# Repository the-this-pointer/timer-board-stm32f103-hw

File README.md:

# Universal Timer Board Hardware
This project is the alpha version for <a href="https://github.com/the-this-pointer/timer-board-stm32f103" target="_blank">this project</a>. It's deprecated and has some blunders in PCB designs that are not fixed in these files.

The newer version of timer hardware is located <a href="https://github.com/the-this-pointer/timer-board-stm32f103-hw-2" target="_blank">here</a>

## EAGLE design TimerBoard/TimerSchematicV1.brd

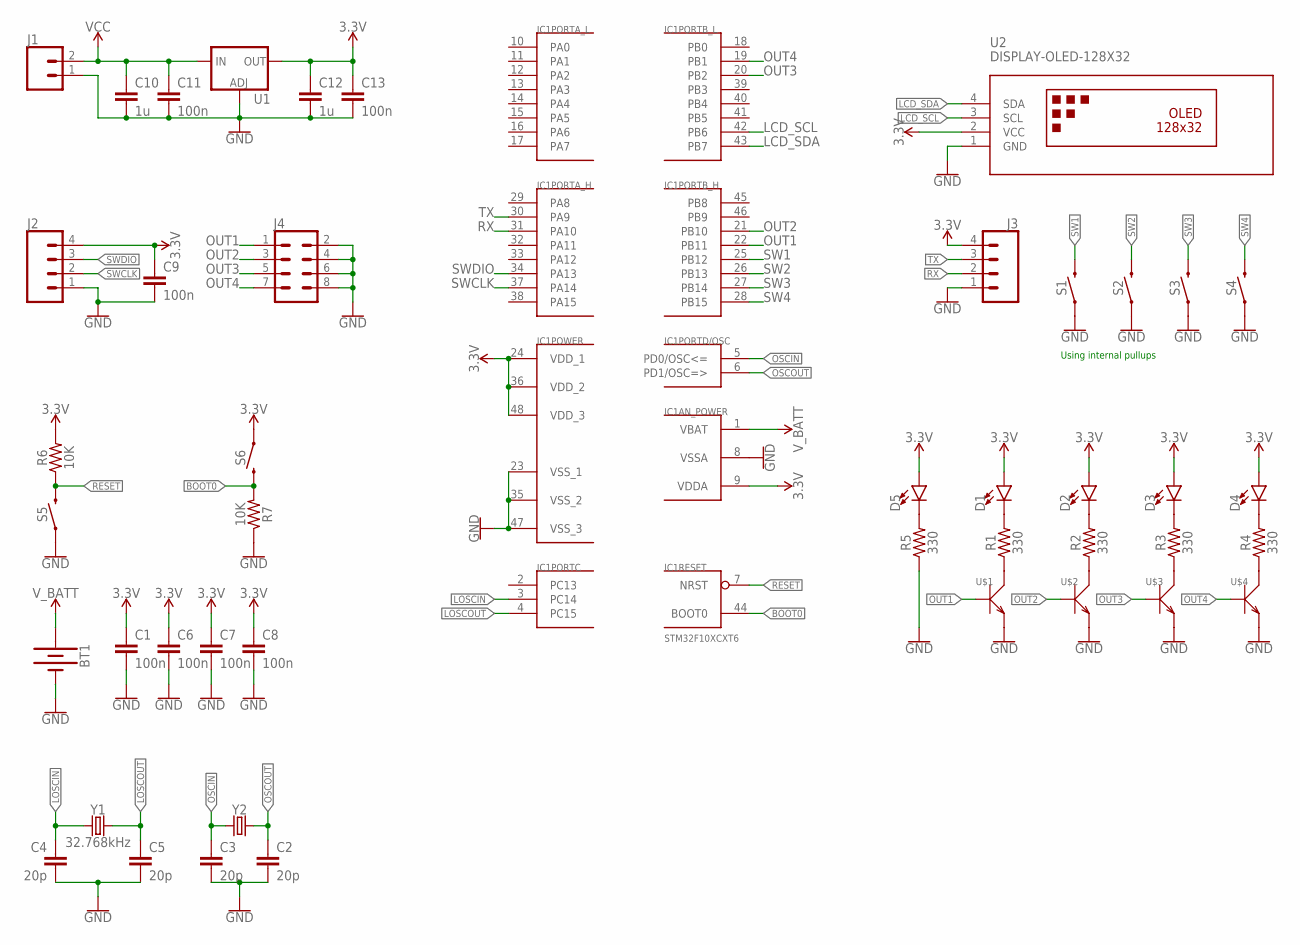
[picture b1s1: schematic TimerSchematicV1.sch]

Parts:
BT1: BATTERY-20MM_PTH; BATTCOM_20MM_PTH
C1, C6, C7, C8, C9, C11, C13: 100n; 1206
C2, C3, C4, C5: 20p; 1206
C10, C12: 1u; 1206
D1, D2, D3, D4, D5: LED1206; LED-1206
IC1: STM32F10XCXT6; TQFP48
J1: CONN_02; 1X02
J2, J3: CONN_04PTH; 1X04
J4: CONN_04X2; 2X4
R1, R2, R3, R4, R5: 330; 1206
R6, R7: 10K; 1206
S1, S2, S3, S4: MOMENTARY-SWITCH-SPST-PTH-6.0MM-KIT; TACTILE_SWITCH_PTH_6.0MM_KIT
S5, S6: MOMENTARY-SWITCH-SPST-SMD-6.0X3.5MM; TACTILE_SWITCH_SMD_6.0X3.5MM
U1: V_REG_LM1117SOT223; SOT223
U2: DISPLAY-OLED-128X32
U$1, U$2, U$3, U$4: MMBT3904LT1G; SOT-23
Y1: 32.768kHz; CRYSTAL-PTH-2X6-CYL-KIT
Y2: CRYSTALSMD-HC49UP; HC49UP

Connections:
3.3V: C1.1, C6.1, C7.1, C8.1, C9.1, C12.1, C13.1, D1.A, D2.A, D3.A, D4.A, D5.A, IC1.9 (VDDA), IC1.24 (VDD_1), IC1.36 (VDD_2), IC1.48 (VDD_3), J2.4, J3.4, R6.2, S6.1, U1.2 (OUT), U1.4 (OUT), U2.2 (VCC)
BOOT0: IC1.44 (BOOT0), R7.2, S6.2
GND: BT1.2 (-), C1.2, C2.2, C3.2, C4.2, C5.2, C6.2, C7.2, C8.2, C9.2, C10.2, C11.2, C12.2, C13.2, IC1.8 (VSSA), IC1.23 (VSS_1), IC1.35 (VSS_2), IC1.47 (VSS_3), J1.1, J2.1, J3.1, J4.2, J4.4, J4.6, J4.8, R5.1, R7.1, S1.1, S2.1, S3.1, S4.1, S5.1, U1.1 (ADJ), U2.1 (GND), U$1.2 (E), U$2.2 (E), U$3.2 (E), U$4.2 (E)
LCD_SCL: IC1.42 (PB6), U2.3 (SCL)
LCD_SDA: IC1.43 (PB7), U2.4 (SDA)
LOSCIN: C4.1, IC1.3 (PC14), Y1.1
LOSCOUT: C5.1, IC1.4 (PC15), Y1.2
unnamed: D1.C, R1.2
unnamed: D2.C, R2.2
unnamed: D3.C, R3.2
unnamed: D4.C, R4.2
unnamed: D5.C, R5.2
unnamed: R1.1, U$1.3 (C)
unnamed: R2.1, U$2.3 (C)
unnamed: R3.1, U$3.3 (C)
unnamed: R4.1, U$4.3 (C)
OSCIN: C3.1, IC1.5 (PD0/OSC<=), Y2.1
OSCOUT: C2.1, IC1.6 (PD1/OSC=>), Y2.2
OUT1: IC1.22 (PB11), J4.1, U$1.1 (B)
OUT2: IC1.21 (PB10), J4.3, U$2.1 (B)
OUT3: IC1.20 (PB2), J4.5, U$3.1 (B)
OUT4: IC1.19 (PB1), J4.7, U$4.1 (B)
RESET: IC1.7 (NRST), R6.1, S5.2
RX: IC1.31 (PA10), J3.2
SW1: IC1.25 (PB12), S1.3 (2)
SW2: IC1.26 (PB13), S2.3 (2)
SW3: IC1.27 (PB14), S3.3 (2)
SW4: IC1.28 (PB15), S4.3 (2)
SWCLK: IC1.37 (PA14), J2.2
SWDIO: IC1.34 (PA13), J2.3
TX: IC1.30 (PA9), J3.3
VCC: C10.1, C11.1, J1.2, U1.3 (IN)
V_BATT: BT1.1 (+), IC1.1 (VBAT)

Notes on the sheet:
Using internal pullups

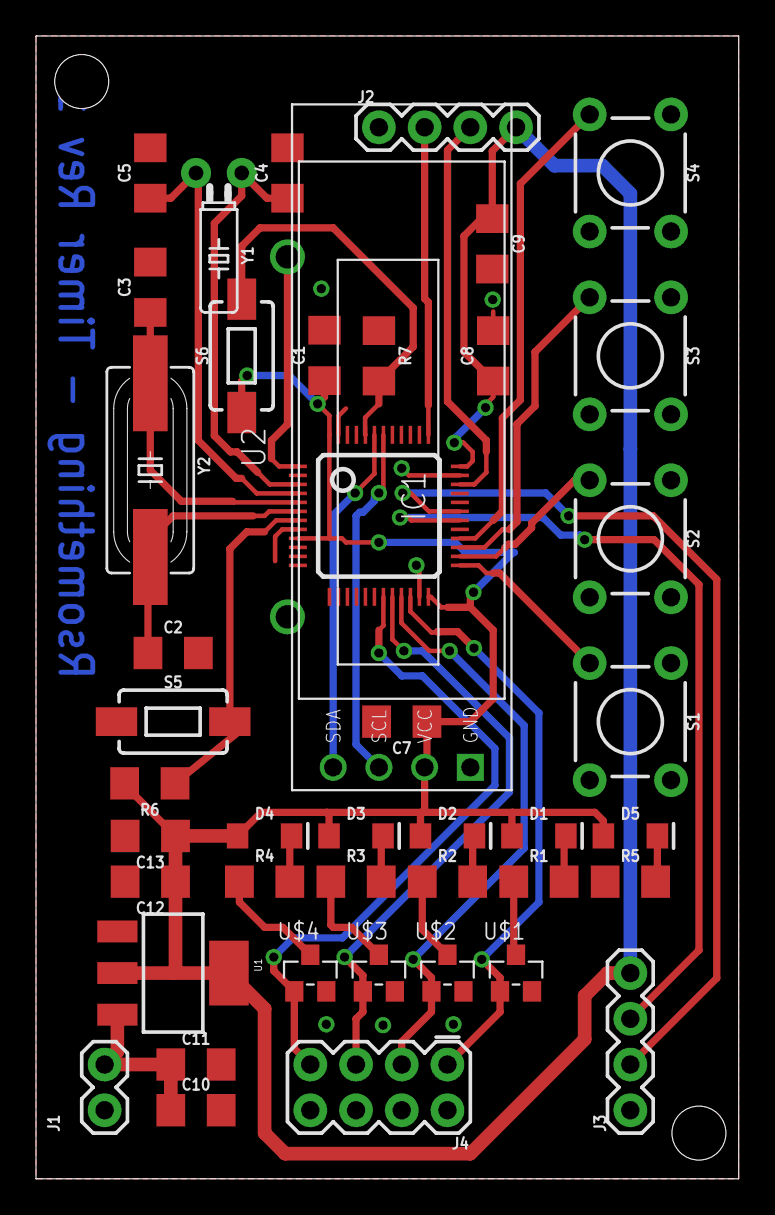
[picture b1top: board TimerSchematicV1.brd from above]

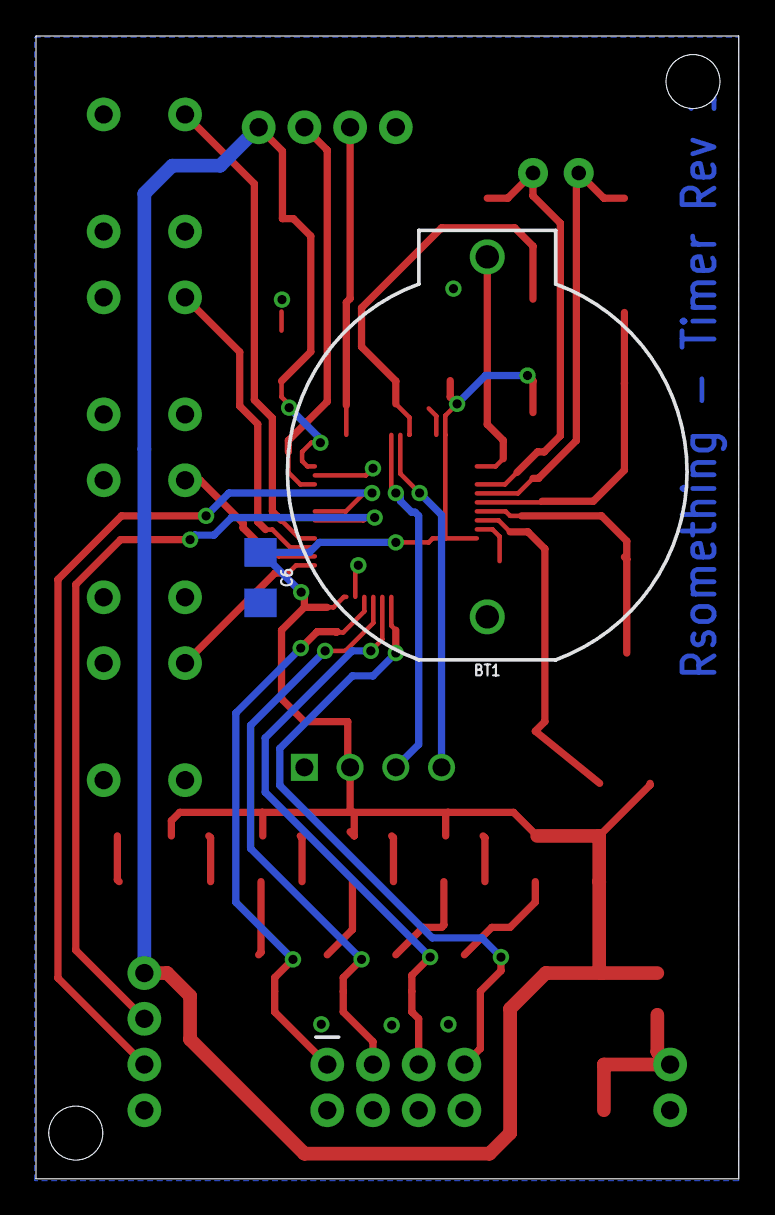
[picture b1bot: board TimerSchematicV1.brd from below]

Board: 2 copper layers, 39.0 x 63.5 mm, 45 parts (2 on the bottom side), 33 nets.

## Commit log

2023-03-18 Schematic Alpha
2023-03-18 PCB alpha created
2023-03-24 readme updated

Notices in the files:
parts and their libraries:
SparkFun-Batteries: Licensing: Creative Commons ShareAlike 4.0 International - https://creativecommons.org/licenses/by-sa/4.0
diy-modules: Released under the Creative Commons Attribution 4.0 International License: http://creativecommons.org/licenses/by/4.0
